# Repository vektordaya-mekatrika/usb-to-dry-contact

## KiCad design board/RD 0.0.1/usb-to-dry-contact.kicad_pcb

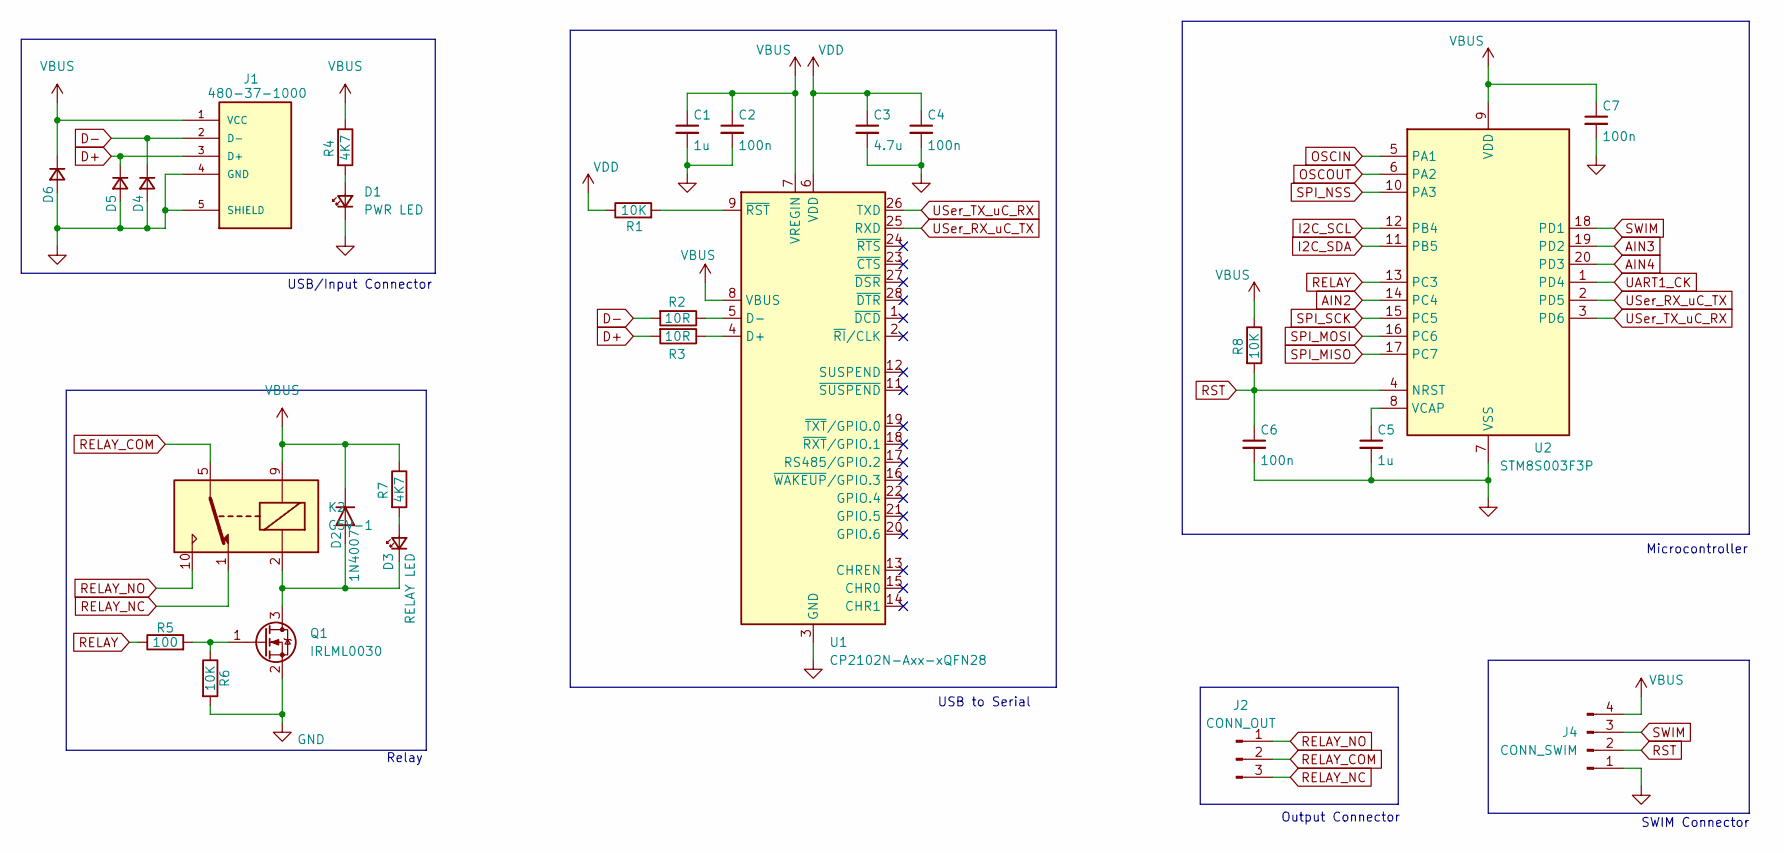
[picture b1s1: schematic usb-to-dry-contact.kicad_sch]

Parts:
C1, C5: 1u; C_0603_1608Metric_Pad1.08x0.95mm_HandSolder; Mfg PN CC0603KRX5R8BB105; LCSC Part # C14664
C2, C4, C6, C7: 100n; C_0603_1608Metric_Pad1.08x0.95mm_HandSolder; Mfg PN CC0603KRX7R9BB104; LCSC Part # C14663
C3: 4.7u; C_0603_1608Metric_Pad1.08x0.95mm_HandSolder; Mfg PN CC0603KRX5R7BB475; LCSC Part # C277476
D1: PWR LED; LED_0603_1608Metric_Pad1.05x0.95mm_HandSolder; Mfg PN LTST-C190GKT; LCSC Part # C125093
D2: 1N4007; D_SOD-123F; Mfg PN 1N4007 A7; LCSC Part # C2902912
D3: RELAY LED; LED_0603_1608Metric_Pad1.05x0.95mm_HandSolder; Mfg PN LTST-C190GKT; LCSC Part # C125093
D4, D5, D6: BZT52B5V1S; D_SOD-323; Mfg PN BZT52B5V1S; LCSC Part # C19077434
J1: 480-37-1000; USB_A_Molex_48037-2200_Horizontal; PARTREV D; LCSC Part # C319178
J2: CONN_OUT; TerminalBlock_Phoenix_MKDS-1,5-3-5.08_1x03_P5.08mm_Horizont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; Mfg PN WJ500V-5.08-3P; LCSC Part # C72334
J4: CONN_SWIM; PinHeader_1x04_P2.54mm_Vertical; Mfg PN HB-PH3-25414PB2GOP; LCSC Part # C6332197
K2: G5V-1; Relay_SPDT_Omron_G5V-1; Mfg PN G5V-1 DC5; LCSC Part # C28695
Q1: IRLML0030; SOT-23; Mfg PN IRLML0030TRPBF; LCSC Part # C67272
R1, R6, R8: 10K; R_0603_1608Metric_Pad0.98x0.95mm_HandSolder; Mfg PN RC0603FR-0710KL; LCSC Part # C98220
R2, R3: 10R; R_0603_1608Metric_Pad0.98x0.95mm_HandSolder; Mfg PN RC0603FR-0710RL; LCSC Part # C109318
R4, R7: 4K7; R_0603_1608Metric_Pad0.98x0.95mm_HandSolder; Mfg PN RC0603JR-074K7L; LCSC Part # C105428
R5: 100; R_0603_1608Metric_Pad0.98x0.95mm_HandSolder; Mfg PN RC0603FR-07100RL; LCSC Part # C105588
U1: CP2102N-Axx-xQFN28; QFN-28-1EP_5x5mm_P0.5mm_EP3.1x3.1mm; Mfg PN CP2102-GMR; LCSC Part # C6568
U2: STM8S003F3P; TSSOP-20_4.4x6.5mm_P0.65mm; Mfg PN STM8S003F3P6TR; LCSC Part # C52717

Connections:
AIN2: U2.14 (PC4)
AIN3: U2.19 (PD2)
AIN4: U2.20 (PD3)
D+: D5.1 (K), J1.3 (D+), R3.2
D-: D4.1 (K), J1.2 (D-), R2.2
GND: C1.2, C2.2, C3.2, C4.2, C5.2, C6.2, C7.2, D1.1 (K), D4.2 (A), D5.2 (A), D6.2 (A), J1.4 (GND), J1.5 (SHIELD), J4.1, Q1.2 (S), R6.2, U1.3 (GND), U1.29 (GND), U2.7 (VSS)
I2C_SCL: U2.12 (PB4)
I2C_SDA: U2.11 (PB5)
unnamed: D1.2 (A), R4.2
unnamed: D2.2 (A), D3.1 (K), K2.2, Q1.3 (D)
unnamed: D3.2 (A), R7.2
unnamed: Q1.1 (G), R5.2, R6.1
unnamed: R3.1, U1.4 (D+)
unnamed: R2.1, U1.5 (D-)
unnamed: R1.2, U1.9 (~RST)
unnamed: C5.1, U2.8 (VCAP)
OSCIN: U2.5 (PA1)
OSCOUT: U2.6 (PA2)
RELAY: R5.1, U2.13 (PC3)
RELAY_COM: J2.2, K2.5, K2.6
RELAY_NC: J2.3, K2.1
RELAY_NO: J2.1, K2.10
RST: C6.1, J4.2, R8.2, U2.4 (NRST)
SPI_MISO: U2.17 (PC7)
SPI_MOSI: U2.16 (PC6)
SPI_NSS: U2.10 (PA3)
SPI_SCK: U2.15 (PC5)
SWIM: J4.3, U2.18 (PD1)
UART1_CK: U2.1 (PD4)
USer_RX_uC_TX: U1.25 (RXD), U2.2 (PD5)
USer_TX_uC_RX: U1.26 (TXD), U2.3 (PD6)
VBUS: C1.1, C2.1, C7.1, D2.1 (K), D6.1 (K), J1.1 (VCC), J4.4, K2.9, R4.1, R7.1, R8.1, U1.7 (VREGIN), U1.8 (VBUS), U2.9 (VDD)
VDD: C3.1, C4.1, R1.1, U1.6 (VDD)

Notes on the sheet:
SWIM Connector
Output Connector
USB/Input Connector
Relay
USB to Serial
Microcontroller

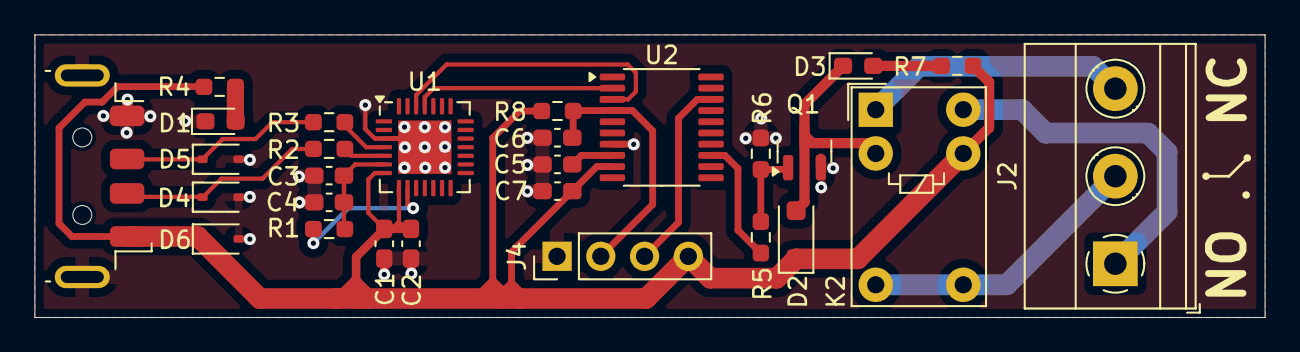
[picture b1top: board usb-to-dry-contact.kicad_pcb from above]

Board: 2 copper layers, 71.4 x 16.4 mm, 28 parts (0 on the bottom side), 21 nets.

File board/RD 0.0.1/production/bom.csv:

Designator,Footprint,Quantity,Value,LCSC Part #
"C1, C5",0603,2,1u,C14664
"C2, C4, C6, C7",0603,4,100n,C14663
C3,0603,1,4.7u,C277476
D1,0603,1,PWR LED,C125093
D2,D_SOD-123F,1,1N4007,C2902912
D3,0603,1,RELAY LED,C125093
"D4, D5, D6",D_SOD-323,3,D_Small,C19077434
J1,USB_A_Molex_48037-2200_Horizontal,1,480-37-1000,C319178
J2,"TerminalBlock_Phoenix_MKDS-1,5-3-5.08_1x03_P5.08mm_Horizontal",1,CONN_OUT,C72334
J4,PinHeader_1x04_P2.54mm_Vertical,1,CONN_SWIM,C6332197
K2,Relay_SPDT_Omron_G5V-1,1,G5V-1,
Q1,SOT-23,1,IRLML0030,C67272
"R1, R6, R8",0603,3,10K,C98220
"R2, R3",0603,2,10R,C109318
"R4, R7",0603,2,4K7,C105428
R5,0603,1,100,C105588
U1,QFN-28-1EP_5x5mm_P0.5mm_EP3.1x3.1mm,1,CP2102N-Axx-xQFN28,C6568
U2,TSSOP-20_4.4x6.5mm_P0.65mm,1,STM8S003F3P,C52717

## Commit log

2024-10-14 First commit
    Add USB connector and CP2102 to schematic
2024-10-14 add relay, output conn, isp conn, avalanche diode
2024-10-16 add STM8 to sch, change the ISP to SWIM connector, place components to board
2024-10-17 Finish to route the board
2024-10-22 Add dry contact software
2024-10-22 add testing procedure
2024-11-08 Change wrong symbol for the Relay MOSFET
    The symbol has switched Drain pin and Source pin
2024-11-08 update production file
